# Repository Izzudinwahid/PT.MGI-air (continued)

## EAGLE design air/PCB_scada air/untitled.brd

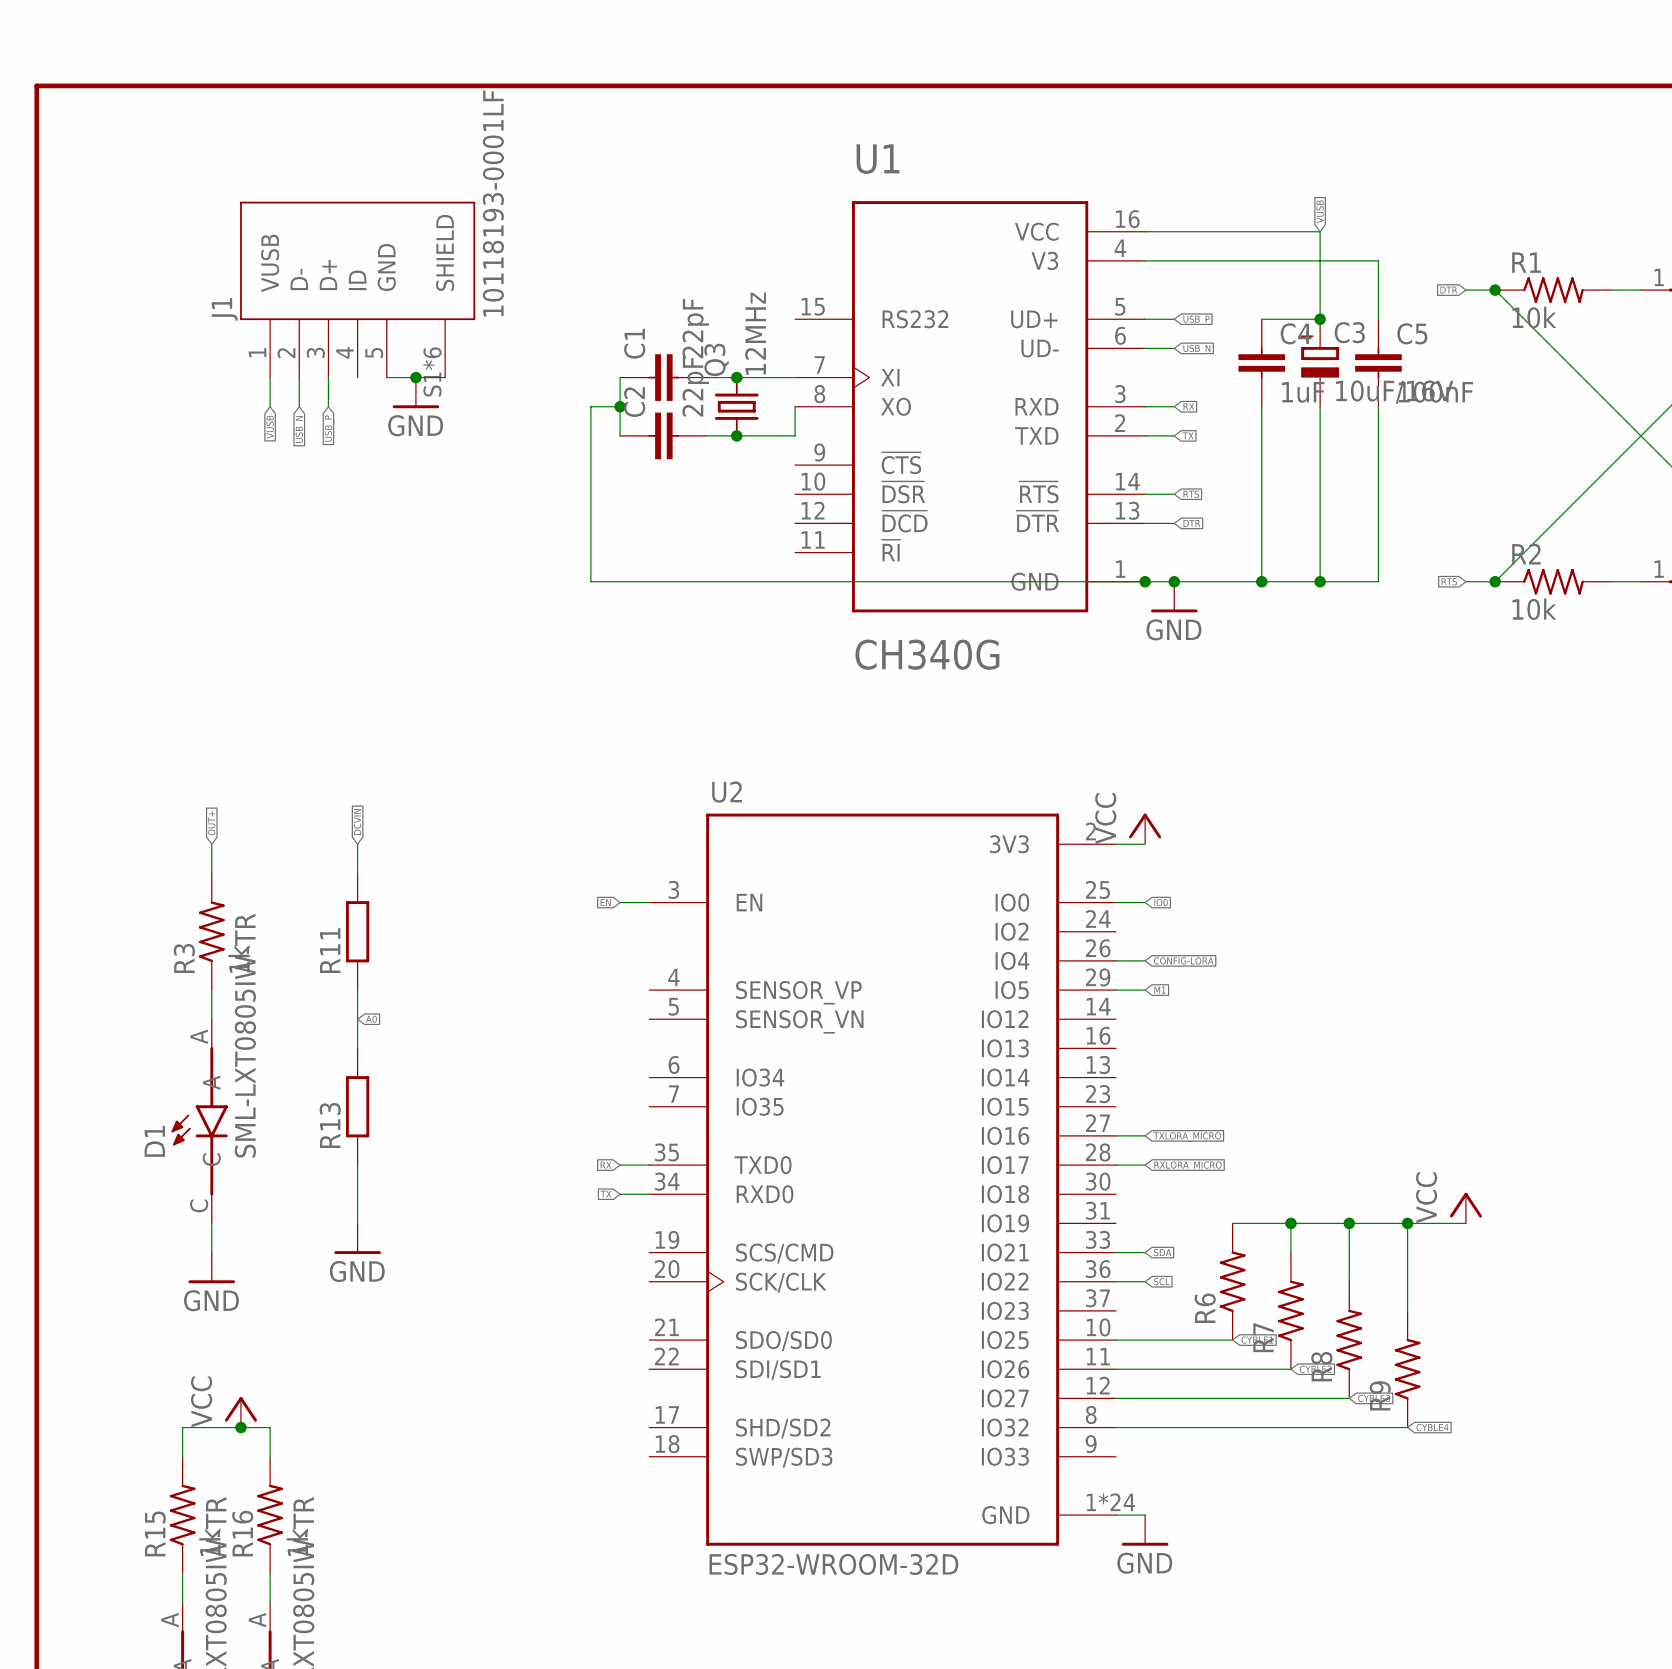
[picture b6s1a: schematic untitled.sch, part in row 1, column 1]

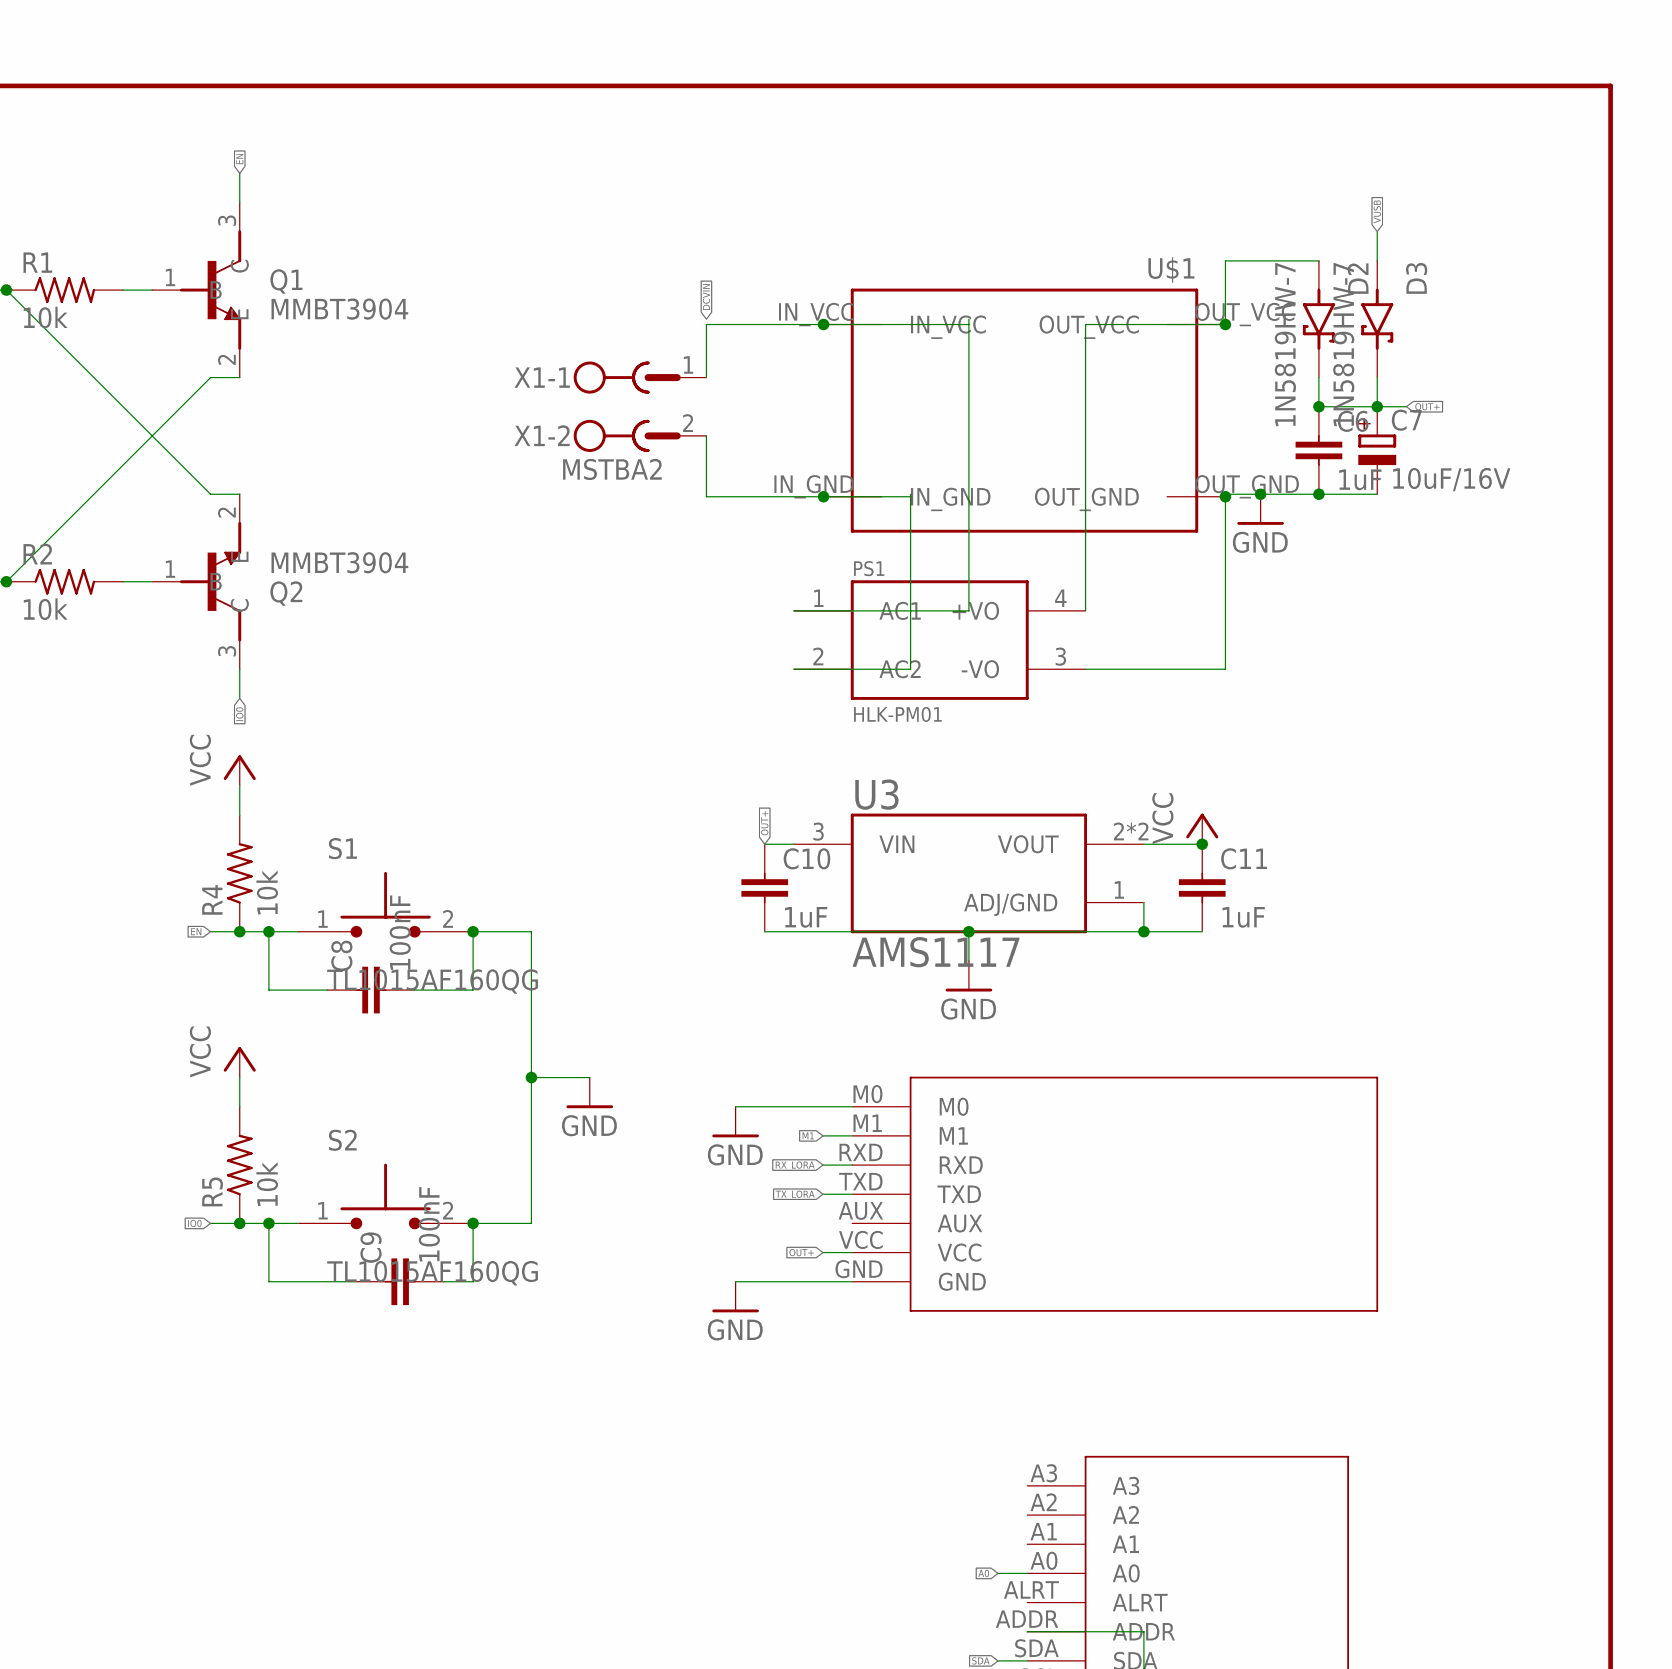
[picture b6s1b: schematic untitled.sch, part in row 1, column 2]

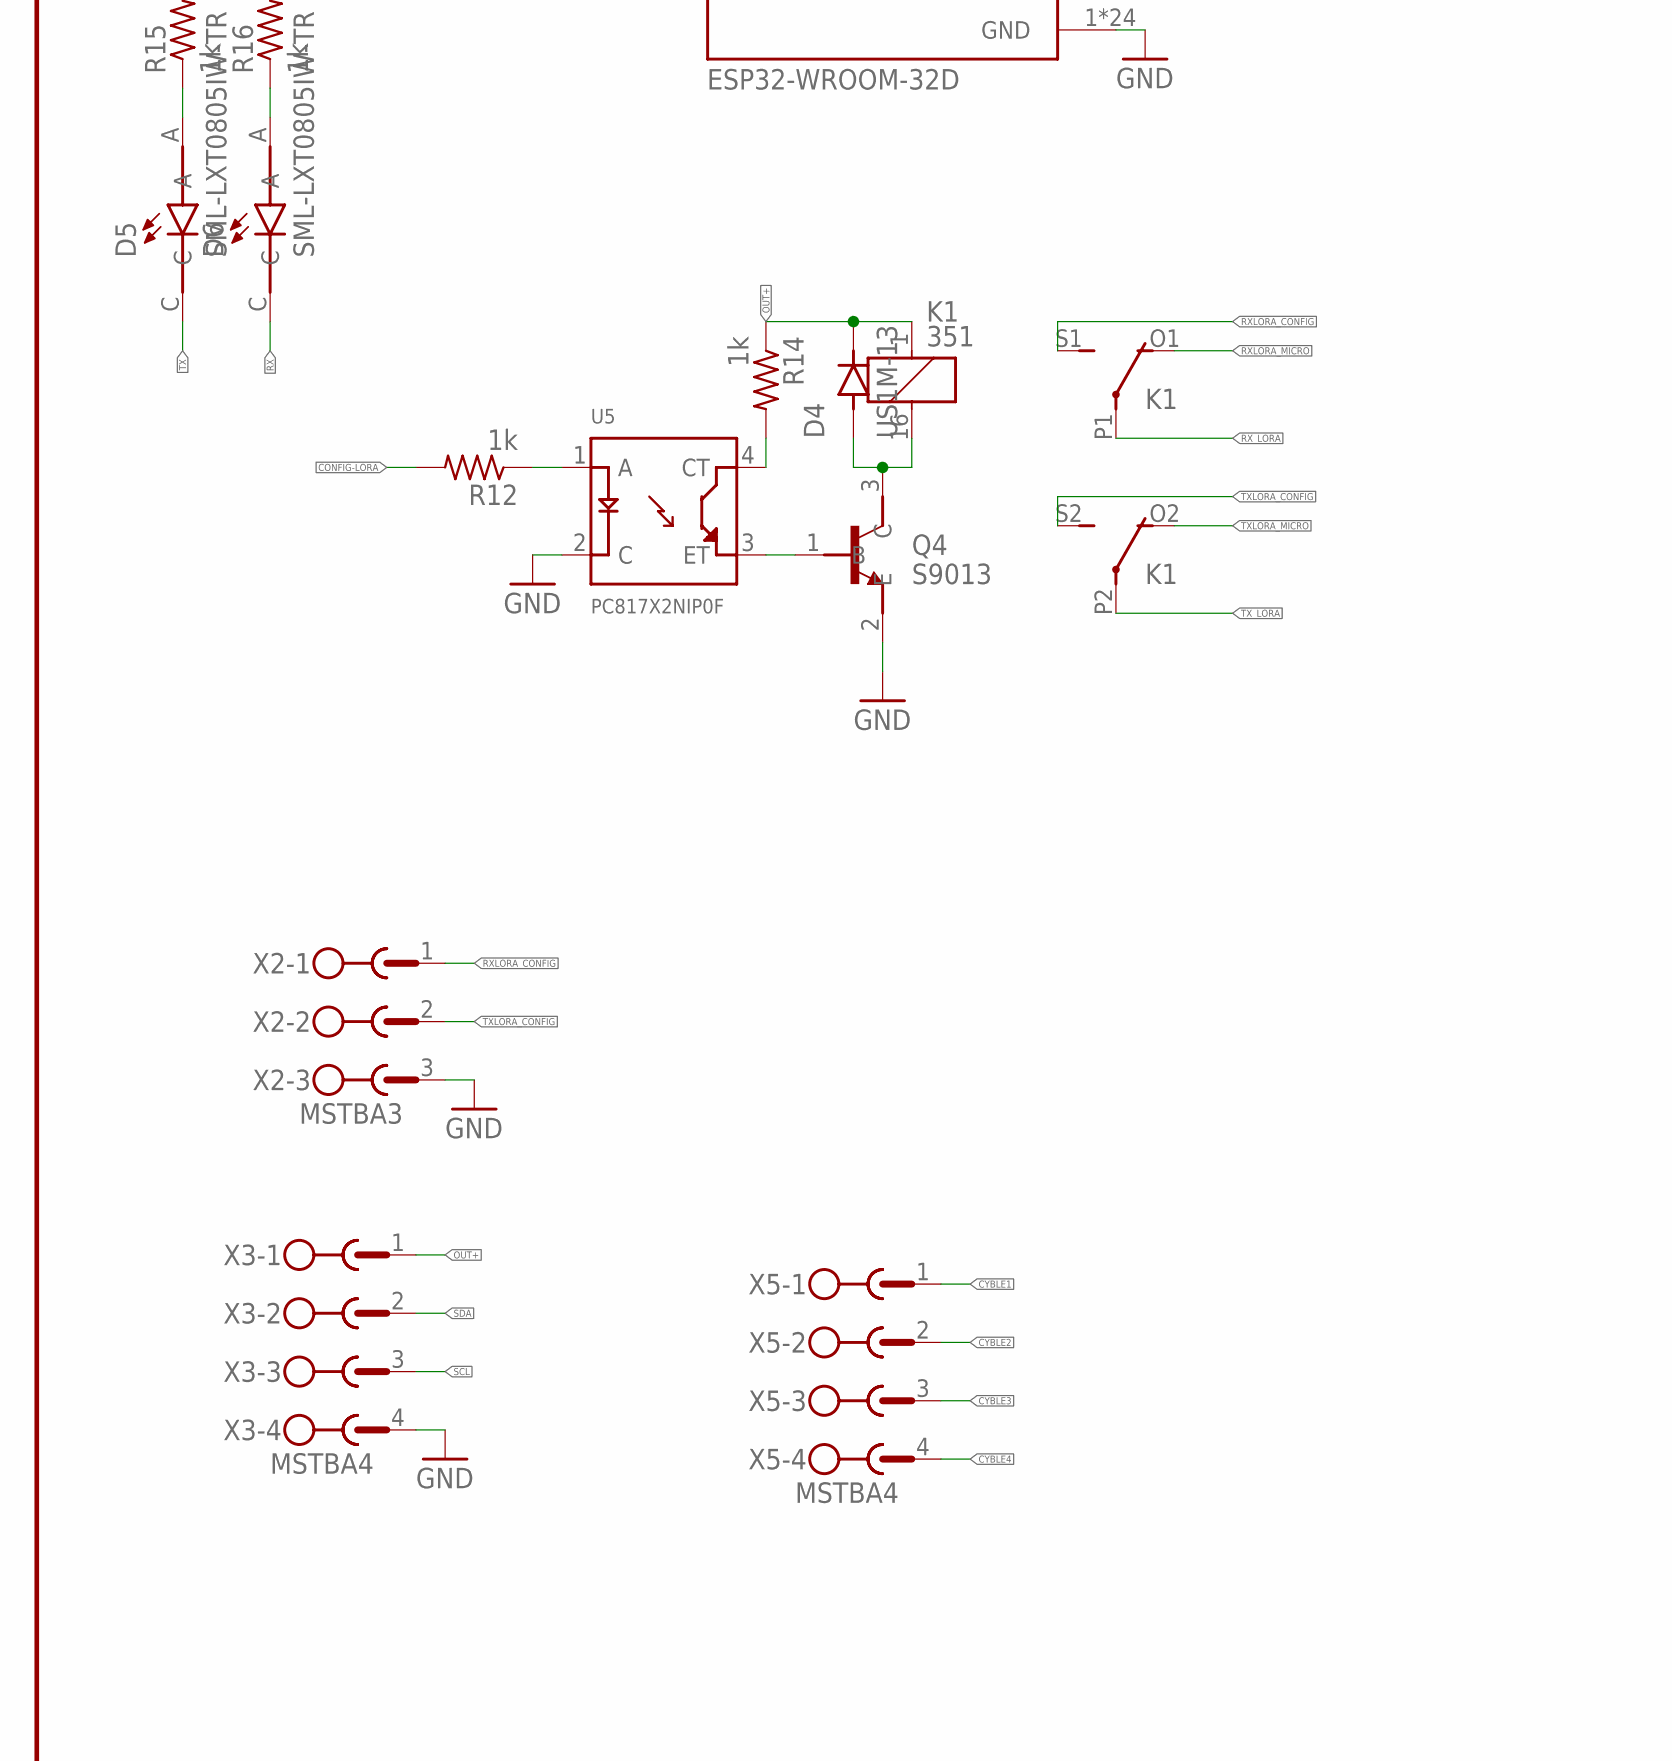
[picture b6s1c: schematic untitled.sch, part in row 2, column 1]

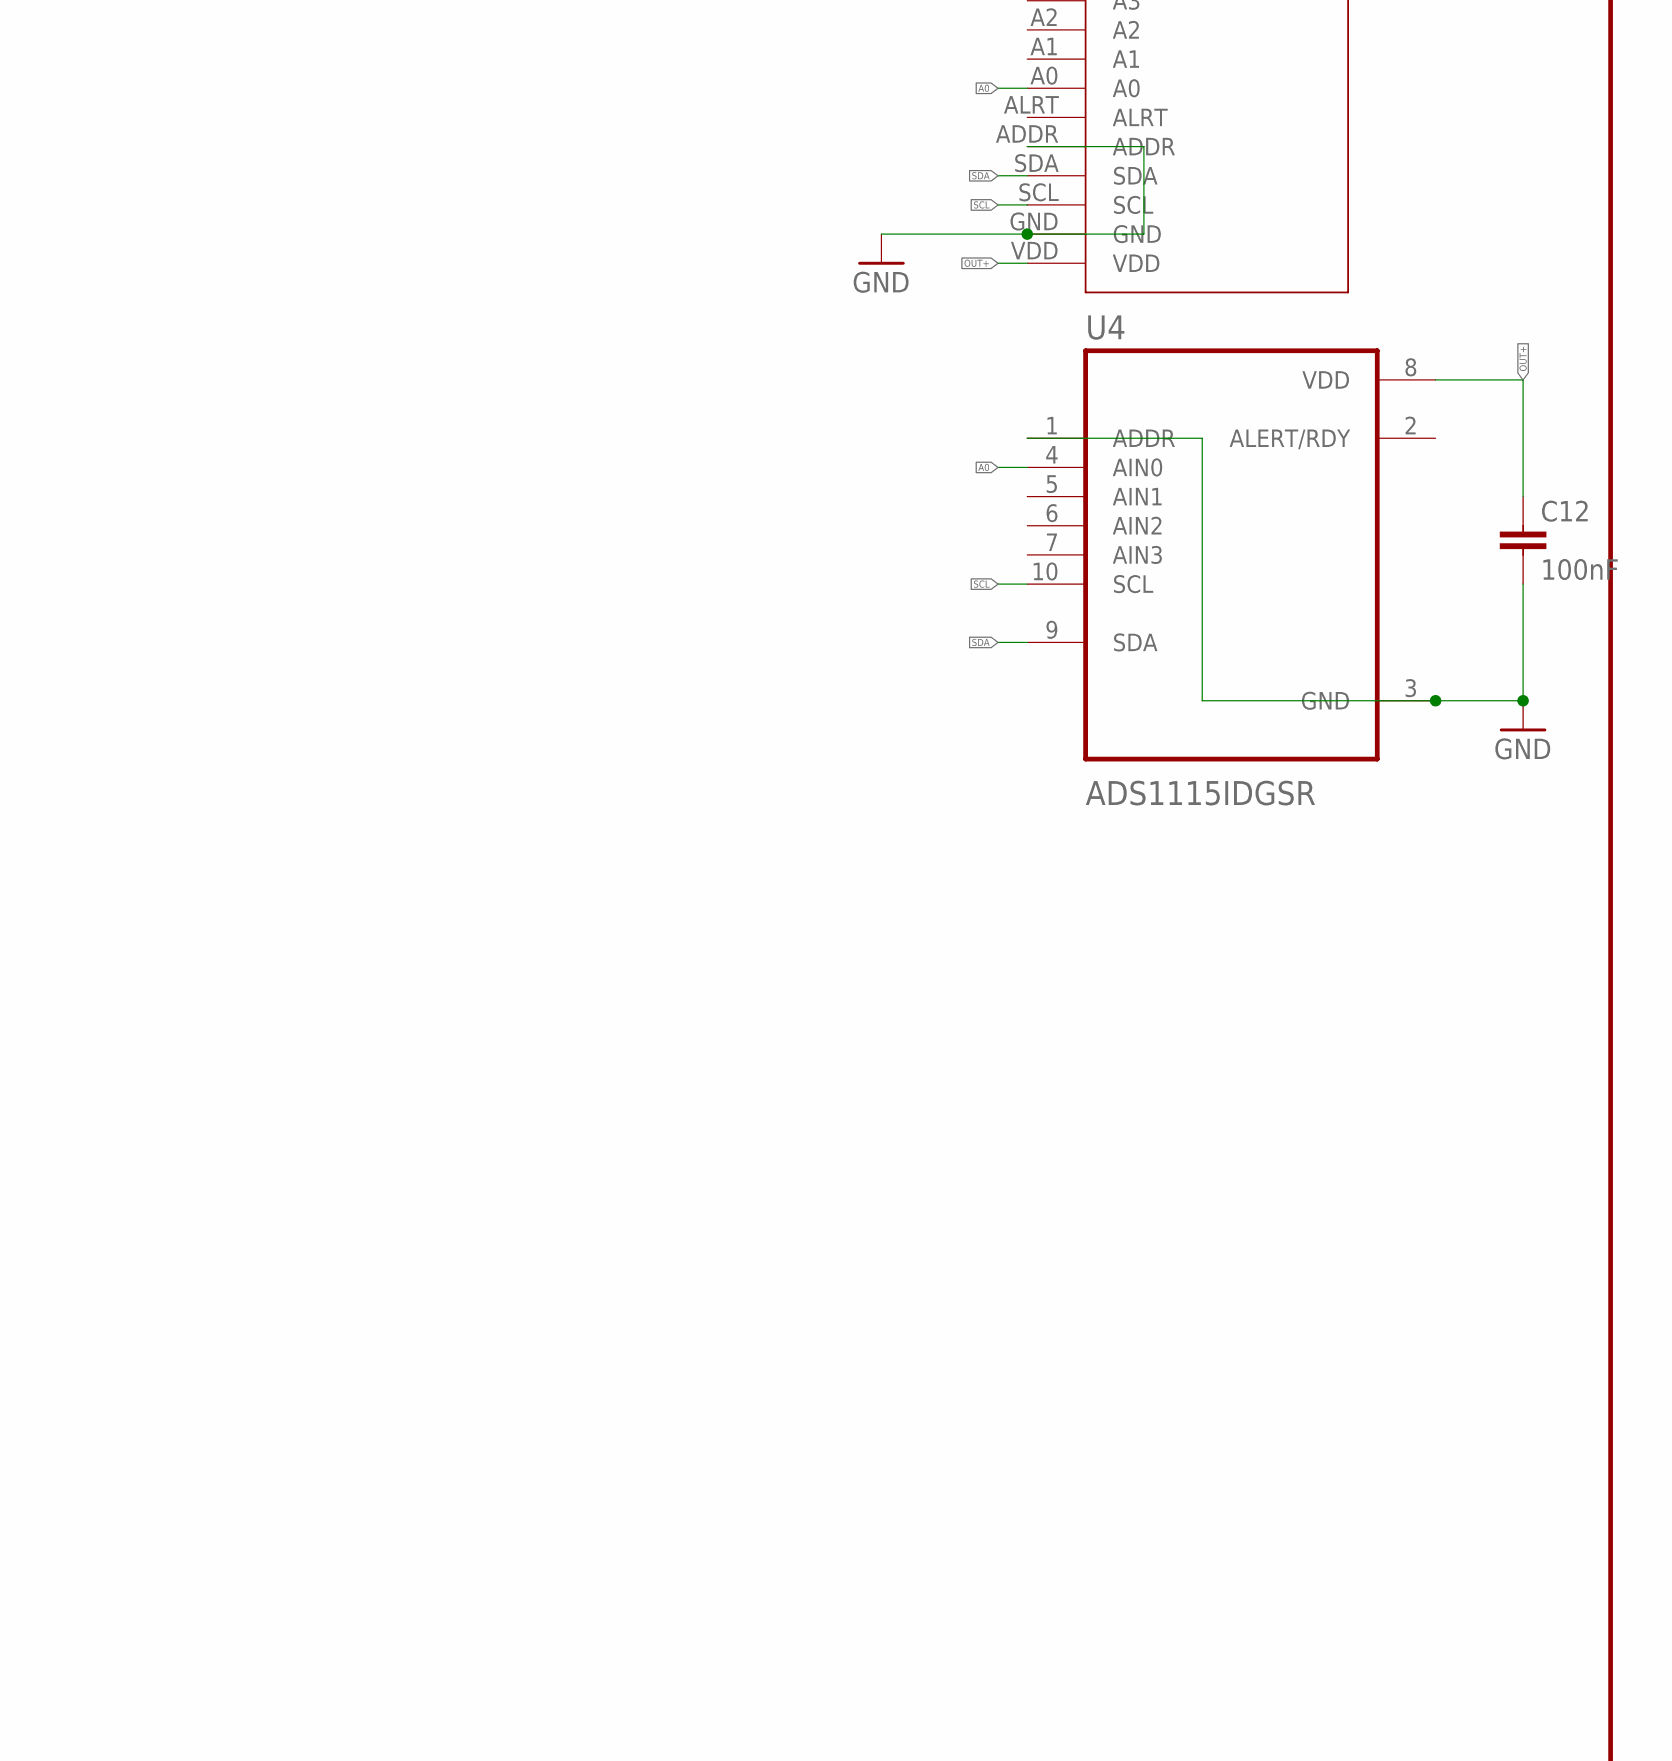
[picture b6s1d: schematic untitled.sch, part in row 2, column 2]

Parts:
ADS1: ADS1115
C1, C2: 22pF; C0805K
C3, C7: 10uF/16V; 153CLV-0505
C4, C6, C10, C11: 1uF; C0805K
C5, C8, C9, C12: 100nF; C0805K
D1, D5, D6: SML-LXT0805IW-TR; LEDC2012X120N
D2, D3: 1N5819HW-7; SOD3715X145N
D4: US1M-13; DIOM5226X240N
EBYTEE220-900T22D1: EBYTEE220-900T22D
J1: 10118193-0001LF; FCI_10118193-0001LF
K1: 351
PS1: HLK-PM01; CONV_HLK-PM01
Q1, Q2: MMBT3904; SOT95P240X120-3N
Q3: 12MHz; SM49
Q4: S9013; SOT95P240X120-3N
R1, R2, R4, R5: 10k; M0805
R3, R12, R14, R15, R16: 1k; M0805
R6, R7, R8, R9: R-US_M0805; M0805
R11, R13: R-EU_0207/12; 0207/12
S1, S2: TL1015AF160QG; SW_TL1015AF160QG
U1: CH340G; SOIC127P600X180-16N
U2: ESP32-WROOM-32D; MODULE_ESP32-WROOM-32D
U3: AMS1117; SOT229P700X180-4N
U4: ADS1115IDGSR; SOP50P490X110-10N
U5: PC817X2NIP0F; SOT254P975X400-4N
U$1: STEPDOWN_SY8205
X1: MSTBA2
X2: MSTBA3
X3, X5: MSTBA4

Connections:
A0: ADS1.A0, R11.1, R13.2, U4.4 (AIN0)
CONFIG-LORA: R12.2, U2.26 (IO4)
CYBLE1: R6.1, U2.10 (IO25), X5.1
CYBLE2: R7.1, U2.11 (IO26), X5.2
CYBLE3: R8.1, U2.12 (IO27), X5.3
CYBLE4: R9.1, U2.8 (IO32), X5.4
DCVIN: PS1.1 (AC1), R11.2, U$1.IN_VCC, X1.1
DTR: Q2.2 (E), R1.1, U1.13 (!DTR)
EN: C8.1, Q1.3 (C), R4.1, S1.1, U2.3 (EN)
GND: ADS1.ADDR, ADS1.GND, C1.1, C2.1, C3.-, C4.2, C5.2, C6.2, C7.-, C8.2, C9.2, C10.2, C11.2, C12.2, D1.C, EBYTEE220-900T22D1.GND, EBYTEE220-900T22D1.M0, J1.5 (GND), J1.S1 (SHIELD), J1.S2 (SHIELD), J1.S3 (SHIELD), J1.S4 (SHIELD), J1.S5 (SHIELD), J1.S6 (SHIELD), PS1.3 (-VO), Q4.2 (E), R13.1, S1.2, S2.2, U1.1 (GND), U2.1 (GND), U2.15 (GND), U2.38 (GND), U2.39_1 (GND), U2.39_2 (GND), U2.39_3 (GND), U2.39_4 (GND), U2.39_5 (GND), U2.39_6 (GND), U2.39_7 (GND), U2.39_8 (GND), U2.39_9 (GND), U2.39_10 (GND), U2.39_11 (GND), U2.39_12 (GND), U2.39_13 (GND), U2.39_14 (GND), U2.39_15 (GND), U2.39_16 (GND), U2.39_17 (GND), U2.39_18 (GND), U2.39_19 (GND), U2.39_20 (GND), U2.39_21 (GND), U3.1 (ADJ/GND), U4.1 (ADDR), U4.3 (GND), U5.2 (C), U$1.OUT_GND, X2.3, X3.4
IO0: C9.1, Q2.3 (C), R5.1, S2.1, U2.25 (IO0)
M1: EBYTEE220-900T22D1.M1, U2.29 (IO5)
unnamed: C1.2, Q3.2, U1.7 (XI)
unnamed: C2.2, Q3.1, U1.8 (XO)
unnamed: Q1.1 (B), R1.2
unnamed: Q2.1 (B), R2.2
unnamed: C5.1, U1.4 (V3)
unnamed: R12.1, U5.1 (A)
unnamed: D2.A, PS1.4 (+VO), U$1.OUT_VCC
unnamed: Q4.1 (B), U5.3 (ET)
unnamed: R14.2, U5.4 (CT)
unnamed: PS1.2 (AC2), U$1.IN_GND, X1.2
unnamed: D1.A, R3.1
unnamed: D5.A, R15.1
unnamed: D4.A, K1.16 (2), Q4.3 (C)
unnamed: D6.A, R16.1
OUT+: ADS1.VDD, C6.1, C7.+, C10.1, C12.1, D2.C (K), D3.C (K), D4.C (K), EBYTEE220-900T22D1.VCC, K1.1, R3.2, R14.1, U3.3 (VIN), U4.8 (VDD), X3.1
RTS: Q1.2 (E), R2.1, U1.14 (!RTS)
RX: D6.C, U1.3 (RXD), U2.35 (TXD0)
RXLORA_CONFIG: K1.S1 (S), X2.1
RXLORA_MICRO: K1.O1 (O), U2.28 (IO17)
RX_LORA: EBYTEE220-900T22D1.RXD, K1.P1
SCL: ADS1.SCL, U2.36 (IO22), U4.10 (SCL), X3.3
SDA: ADS1.SDA, U2.33 (IO21), U4.9 (SDA), X3.2
TX: D5.C, U1.2 (TXD), U2.34 (RXD0)
TXLORA_CONFIG: K1.S2 (S), X2.2
TXLORA_MICRO: K1.O2 (O), U2.27 (IO16)
TX_LORA: EBYTEE220-900T22D1.TXD, K1.P2
USB_N: J1.2 (D-), U1.6 (UD-)
USB_P: J1.3 (D+), U1.5 (UD+)
VCC: C11.1, R4.2, R5.2, R6.2, R7.2, R8.2, R9.2, R15.2, R16.2, U2.2 (3V3), U3.2 (VOUT), U3.4 (VOUT)
VUSB: C3.+, C4.1, D3.A, J1.1 (VUSB), U1.16 (VCC)

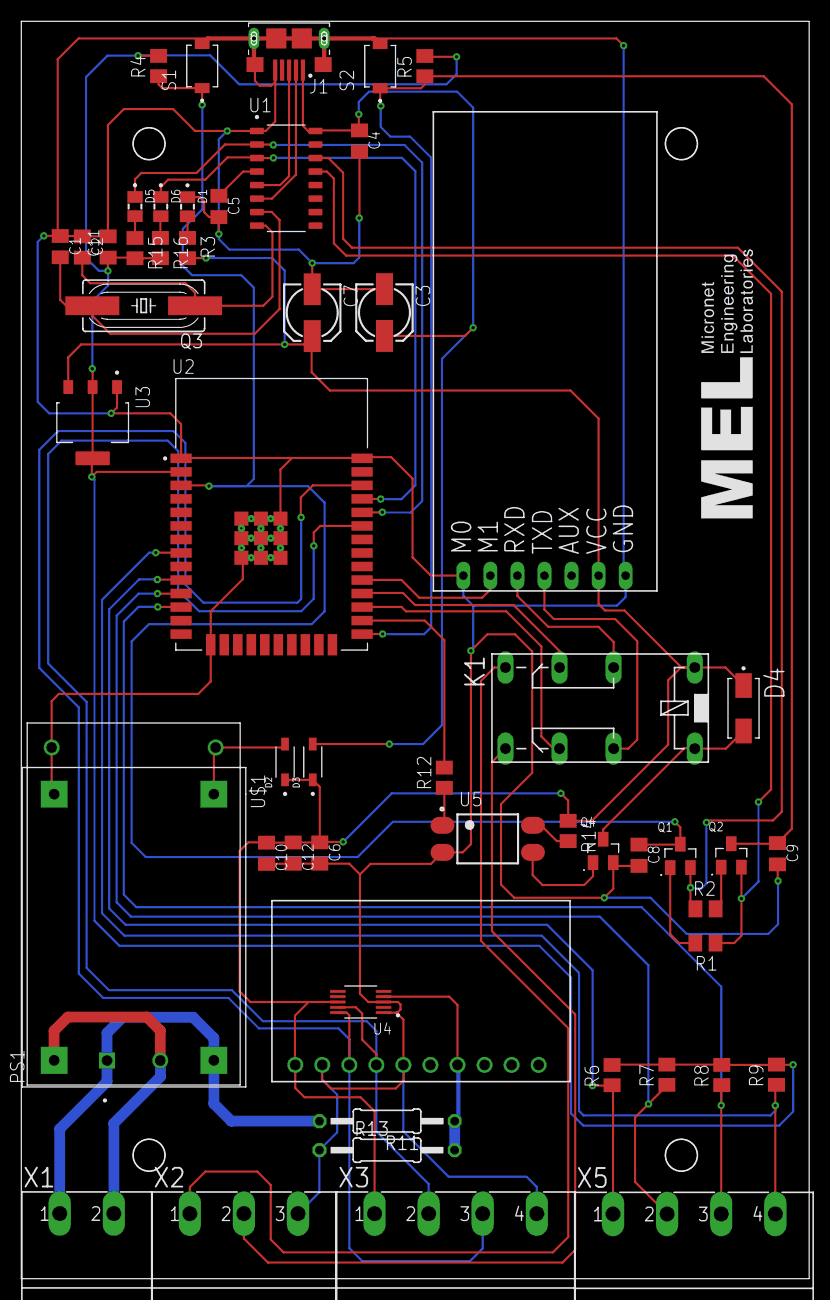
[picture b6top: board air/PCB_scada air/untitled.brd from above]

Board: 2 copper layers, 74.0 x 118.1 mm, 54 parts (0 on the bottom side), 42 nets.
